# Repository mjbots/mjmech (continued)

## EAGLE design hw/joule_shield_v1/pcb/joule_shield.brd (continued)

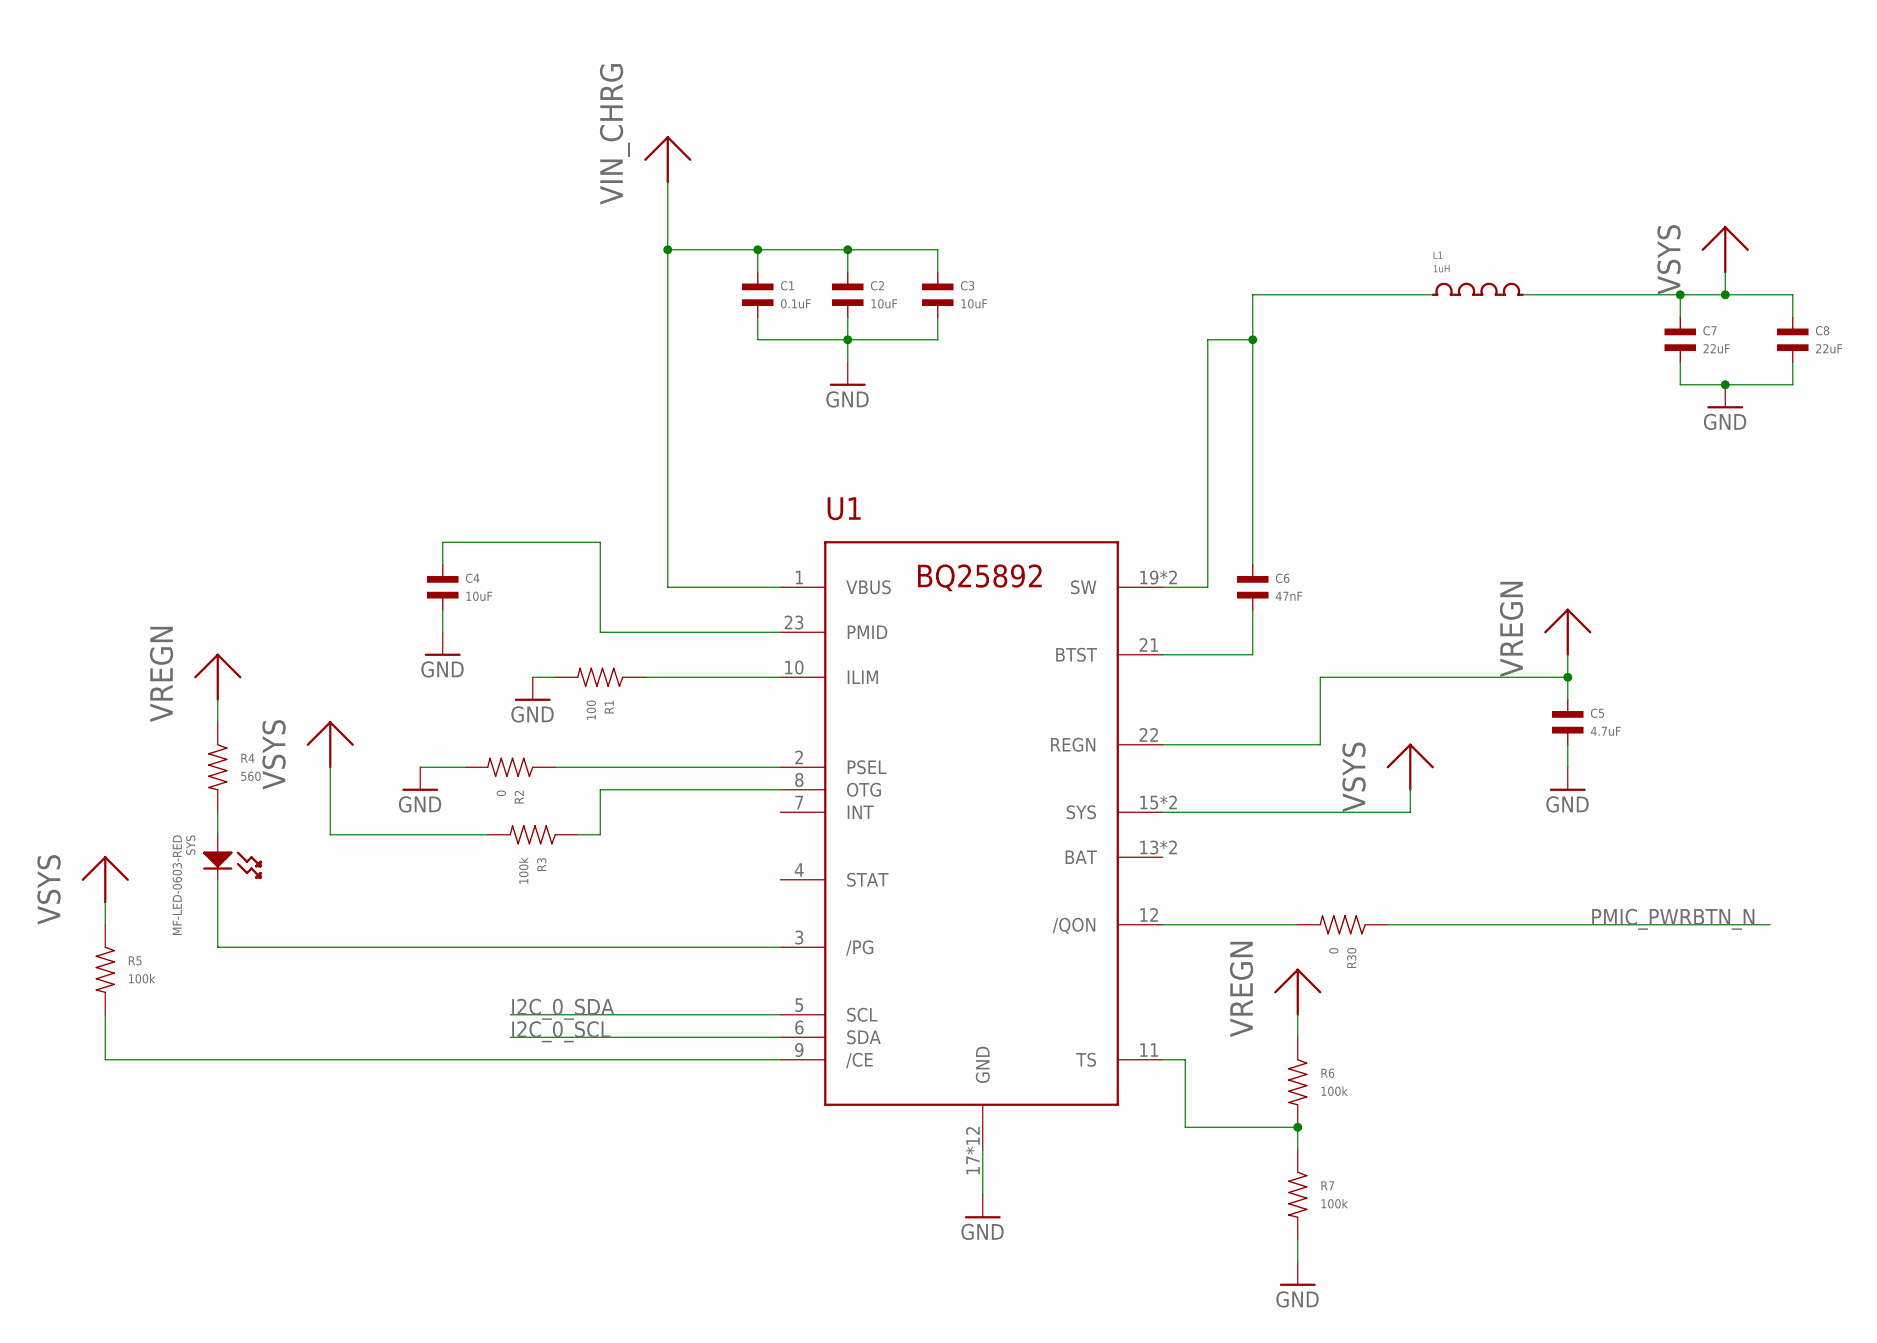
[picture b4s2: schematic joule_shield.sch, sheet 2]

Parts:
C1: 0.1uF; C0603; MPN MF-CAP-0603-0.1uF
C2, C3, C4: 10uF; C0603; MPN C1608X5R1E106M080AC
C5: 4.7uF; C0603; MPN C1608X5R1E475M080AC
C6: 47nF; C0603; MPN CGA3E2X5R1H473M080AA
C7, C8: 22uF; C0603; MPN CL10A226MP8NUNE
L1: 1uH; SPM4012; MPN SPM4012T-1R0M
R1: 100; R0603; MPN MF-RES-0603-100
R2, R30: 0; R0603; MPN MF-RES-0603-0
R3, R5, R6, R7: 100k; R0603; MPN MF-RES-0603-100K
R4: 560; R0603; MPN MF-RES-0603-560
SYS: MF-LED-0603-RED; LED0603
U1: BQ25892PWQFN-24; PWQFN-24; MPN BQ25892RTWT

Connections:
GND: C1.P$2, C2.P$2, C3.P$2, C4.P$2, C5.P$2, C7.P$2, C8.P$2, R1.P$2, R2.P$2, R7.P$2, U1.17 (GND), U1.18 (GND), U1.G0 (GND), U1.G1 (GND), U1.G2 (GND), U1.G3 (GND), U1.G4 (GND), U1.G5 (GND), U1.G6 (GND), U1.G7 (GND), U1.G8 (GND), U1.G9 (GND); also elsewhere on the board
I2C_0_SCL: U1.6 (SDA); also elsewhere on the board
I2C_0_SDA: U1.5 (SCL); also elsewhere on the board
unnamed: R4.P$2, SYS.ANODE
unnamed: C4.P$1, U1.23 (PMID)
unnamed: R1.P$1, U1.10 (ILIM)
unnamed: R2.P$1, U1.2 (PSEL)
unnamed: R3.P$1, U1.8 (OTG)
unnamed: SYS.CATHODE, U1.3 (/PG)
unnamed: R6.P$2, R7.P$1, U1.11 (TS)
unnamed: R5.P$2, U1.9 (/CE)
unnamed: C6.P$2, U1.21 (BTST)
unnamed: C6.P$1, L1.1, U1.19 (SW), U1.20 (SW)
unnamed: R30.P$2, U1.12 (/QON)
PMIC_PWRBTN_N: R30.P$1; also elsewhere on the board
VIN_CHRG: C1.P$1, C2.P$1, C3.P$1, U1.1 (VBUS); also elsewhere on the board
VREGN: C5.P$1, R4.P$1, R6.P$1, U1.22 (REGN)
VSYS: C7.P$1, C8.P$1, L1.2, R3.P$2, R5.P$1, U1.15 (SYS), U1.16 (SYS); also elsewhere on the board

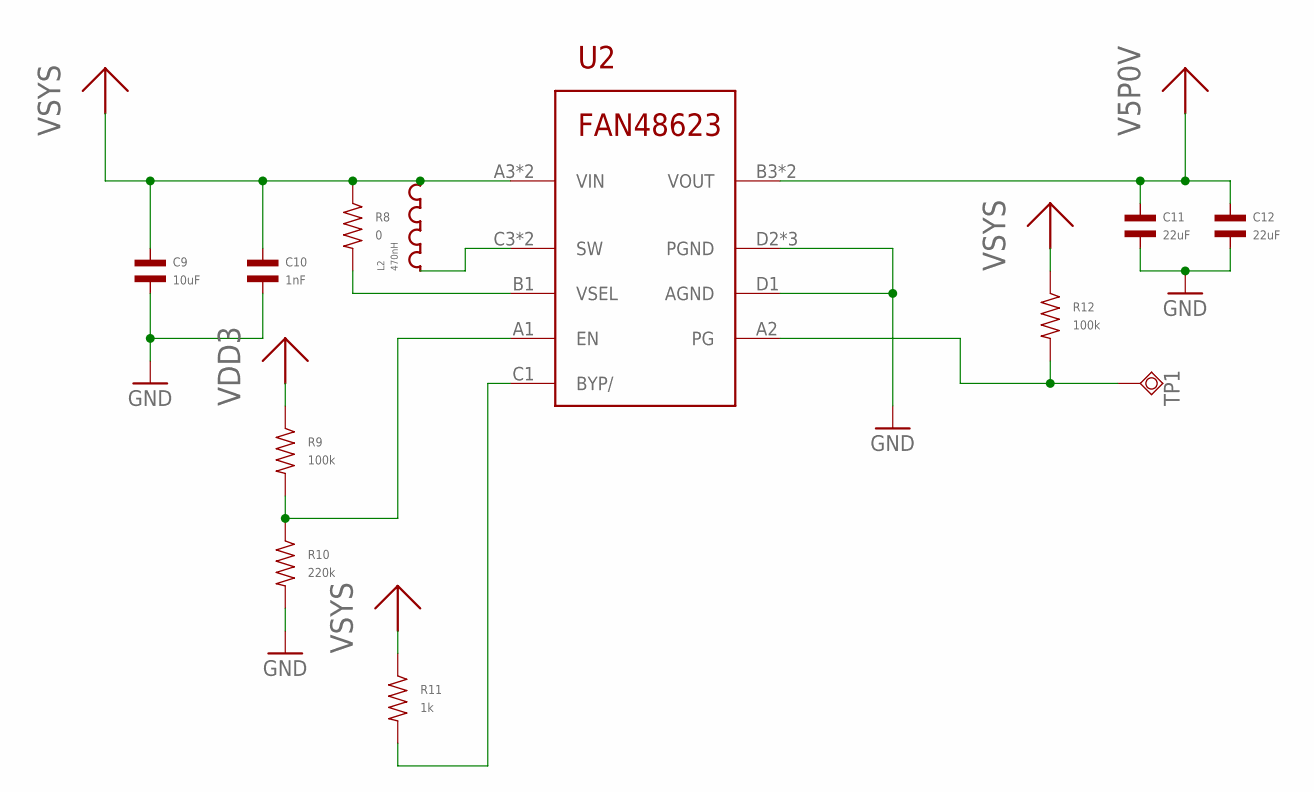
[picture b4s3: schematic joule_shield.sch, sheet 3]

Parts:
C9: 10uF; C0603; MPN C1608X5R1E106M080AC
C10: 1nF; C0603; MPN MF-CAP-0603-1nF
C11, C12: 22uF; C0603; MPN CL10A226MP8NUNE
L2: 470nH; DFE252010P; MPN DFE252010P-R47M=P2
R8: 0; R0603; MPN MF-RES-0603-0
R9, R12: 100k; R0603; MPN MF-RES-0603-100K
R10: 220k; R0603; MPN MF-RES-0603-220K
R11: 1k; R0603; MPN MF-RES-0603-1K
TP1: TPSQB1,27; B1,27
U2: FAN8623WLCSP16; WLCSP16; MPN FAN48623UC50X

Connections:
GND: C9.P$2, C10.P$2, C11.P$2, C12.P$2, R10.P$2, U2.D1 (AGND), U2.D2 (PGND), U2.D3 (PGND), U2.D4 (PGND); also elsewhere on the board
unnamed: R8.P$2, U2.B1 (VSEL)
unnamed: L2.1, U2.C3 (SW), U2.C4 (SW)
unnamed: R9.P$2, R10.P$1, U2.A1 (EN)
unnamed: R11.P$2, U2.C1 (BYP/)
unnamed: R12.P$2, TP1.TP, U2.A2 (PG)
V5P0V: C11.P$1, C12.P$1, U2.B3 (VOUT), U2.B4 (VOUT); also elsewhere on the board
VDD3: R9.P$1; also elsewhere on the board
VSYS: C9.P$1, C10.P$1, L2.2, R8.P$1, R11.P$1, R12.P$1, U2.A3 (VIN), U2.A4 (VIN); also elsewhere on the board

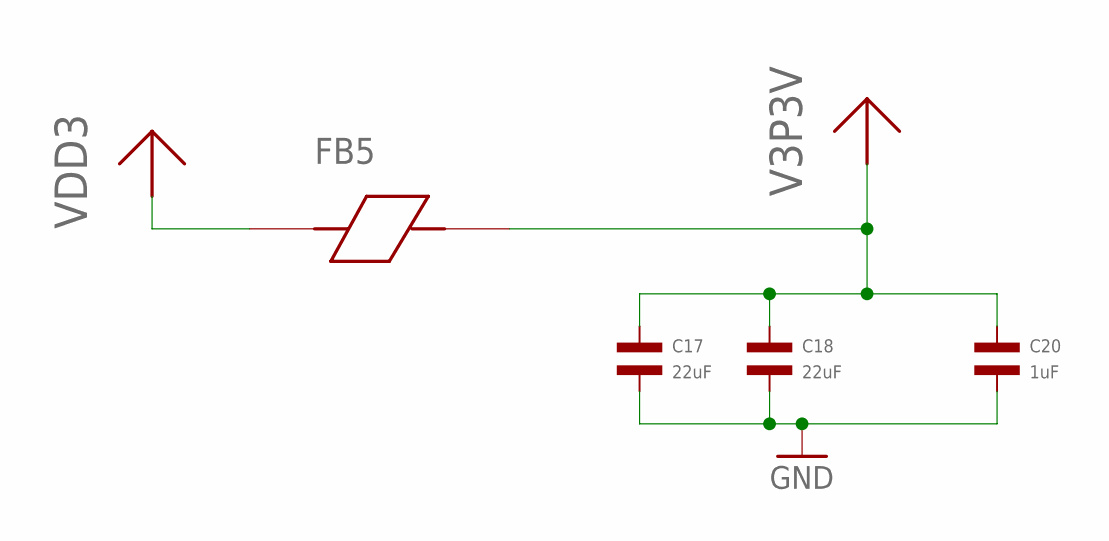
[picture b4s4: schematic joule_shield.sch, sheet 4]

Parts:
C17, C18: 22uF; C0603; MPN CL10A226MP8NUNE
C20: 1uF; C0603; MPN MF-CAP-0603-1uF
FB5: FERRITE_BEAD; R0603; MPN BLM15PD121SN1D

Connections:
GND: C17.P$2, C18.P$2, C20.P$2; also elsewhere on the board
V3P3V: C17.P$1, C18.P$1, C20.P$1, FB5.P$2; also elsewhere on the board
VDD3: FB5.P$1; also elsewhere on the board

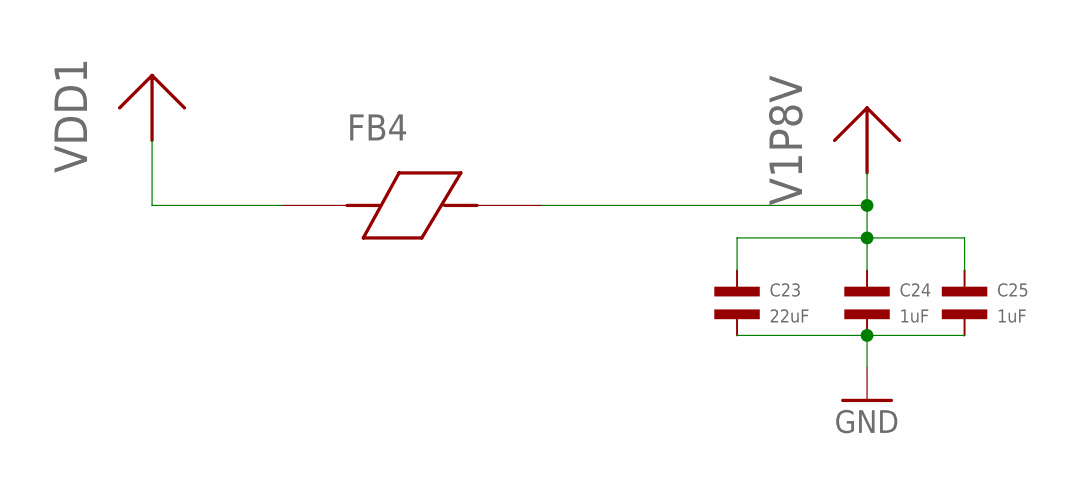
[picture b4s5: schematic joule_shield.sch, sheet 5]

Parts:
C23: 22uF; C0603; MPN CL10A226MP8NUNE
C24, C25: 1uF; C0603; MPN MF-CAP-0603-1uF
FB4: FERRITE_BEAD; R0603; MPN BLM15PD121SN1D

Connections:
GND: C23.P$2, C24.P$2, C25.P$2; also elsewhere on the board
V1P8V: C23.P$1, C24.P$1, C25.P$1, FB4.P$2; also elsewhere on the board
VDD1: FB4.P$1; also elsewhere on the board

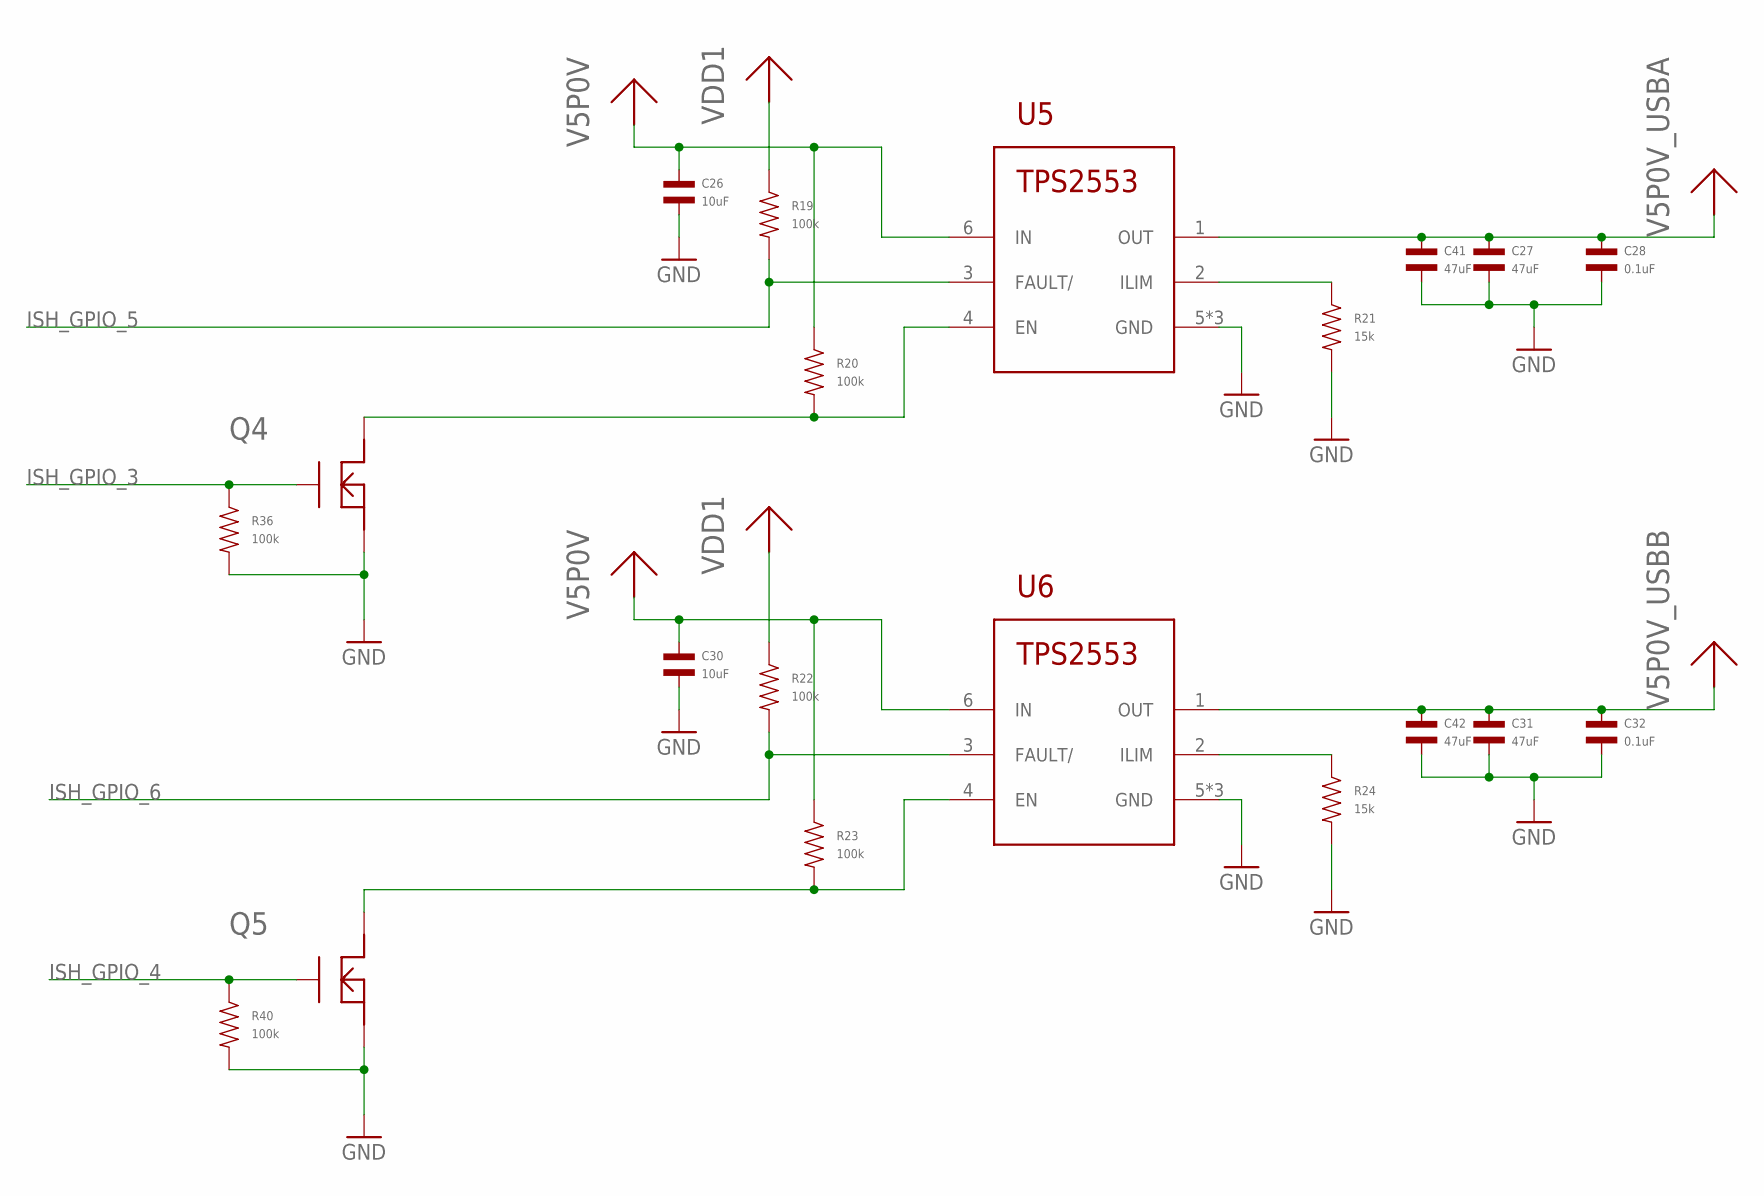
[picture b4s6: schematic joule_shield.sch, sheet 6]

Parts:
C26, C30: 10uF; C0603; MPN C1608X5R1E106M080AC
C27, C31, C41, C42: 47uF; C0805; MPN C2012X5R1A476M125AC
C28, C32: 0.1uF; C0603; MPN MF-CAP-0603-0.1uF
Q4, Q5: NFETEMT3F; EMT3F; MPN RE1C002UNTCL
R19, R20, R22, R23, R36, R40: 100k; R0603; MPN MF-RES-0603-100K
R21, R24: 15k; R0603; MPN MF-RES-0603-15K
U5, U6: TPS2553PWSON-6; PWSON-6; MPN TPS2553DRVT

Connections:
GND: C26.P$2, C27.P$2, C28.P$2, C30.P$2, C31.P$2, C32.P$2, C41.P$2, C42.P$2, Q4.2 (S), Q5.2 (S), R21.P$2, R24.P$2, R36.P$2, R40.P$2, U5.5 (GND), U5.G0 (GND), U5.G1 (GND), U6.5 (GND), U6.G0 (GND), U6.G1 (GND); also elsewhere on the board
ISH_GPIO_3: Q4.1 (G), R36.P$1; also elsewhere on the board
ISH_GPIO_4: Q5.1 (G), R40.P$1; also elsewhere on the board
ISH_GPIO_5: R19.P$2, U5.3 (FAULT/); also elsewhere on the board
ISH_GPIO_6: R22.P$2, U6.3 (FAULT/); also elsewhere on the board
unnamed: Q4.3 (D), R20.P$2, U5.4 (EN)
unnamed: R21.P$1, U5.2 (ILIM)
unnamed: Q5.3 (D), R23.P$2, U6.4 (EN)
unnamed: R24.P$1, U6.2 (ILIM)
V5P0V: C26.P$1, C30.P$1, R20.P$1, R23.P$1, U5.6 (IN), U6.6 (IN); also elsewhere on the board
V5P0V_USBA: C27.P$1, C28.P$1, C41.P$1, U5.1 (OUT); also elsewhere on the board
V5P0V_USBB: C31.P$1, C32.P$1, C42.P$1, U6.1 (OUT); also elsewhere on the board
VDD1: R19.P$1, R22.P$1; also elsewhere on the board

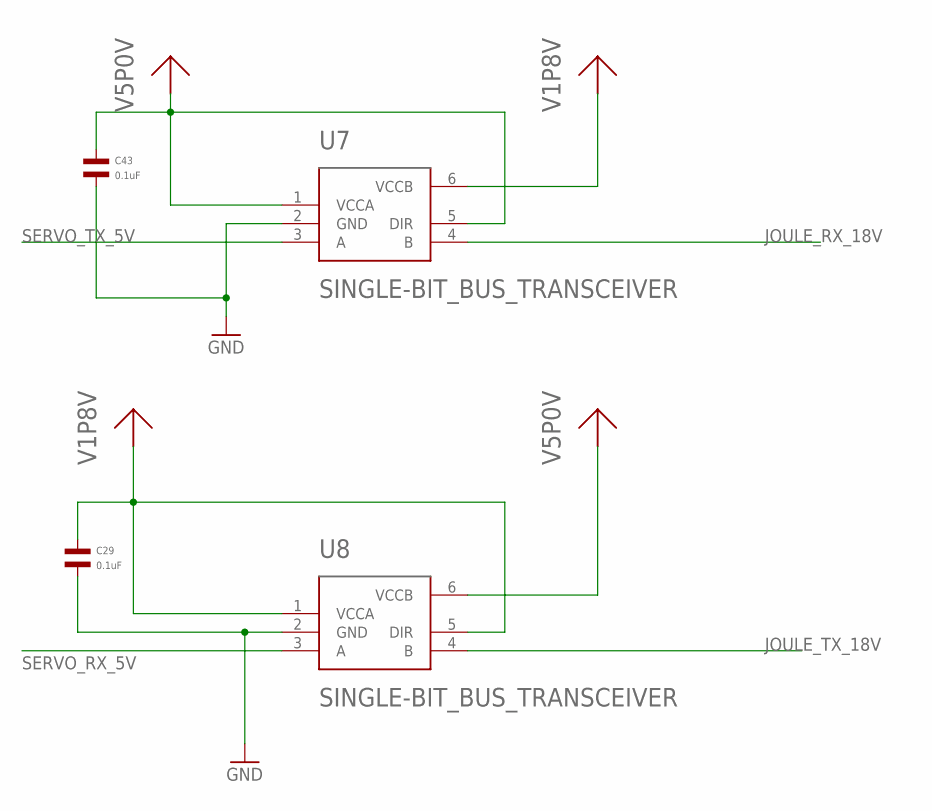
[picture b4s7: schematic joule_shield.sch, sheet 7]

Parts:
C29, C43: 0.1uF; C0603; MPN MF-CAP-0603-0.1uF
U7, U8: SINGLE-BIT_BUS_TRANSCEIVER; SOT23-6; MPN SN74LVC1T45DBVR

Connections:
GND: C29.P$2, C43.P$2, U7.2 (GND), U8.2 (GND); also elsewhere on the board
JOULE_RX_18V: U7.4 (B); also elsewhere on the board
JOULE_TX_18V: U8.4 (B); also elsewhere on the board
SERVO_RX_5V: U8.3 (A); also elsewhere on the board
SERVO_TX_5V: U7.3 (A); also elsewhere on the board
V1P8V: C29.P$1, U7.6 (VCCB), U8.1 (VCCA), U8.5 (DIR); also elsewhere on the board
V5P0V: C43.P$1, U7.1 (VCCA), U7.5 (DIR), U8.6 (VCCB); also elsewhere on the board

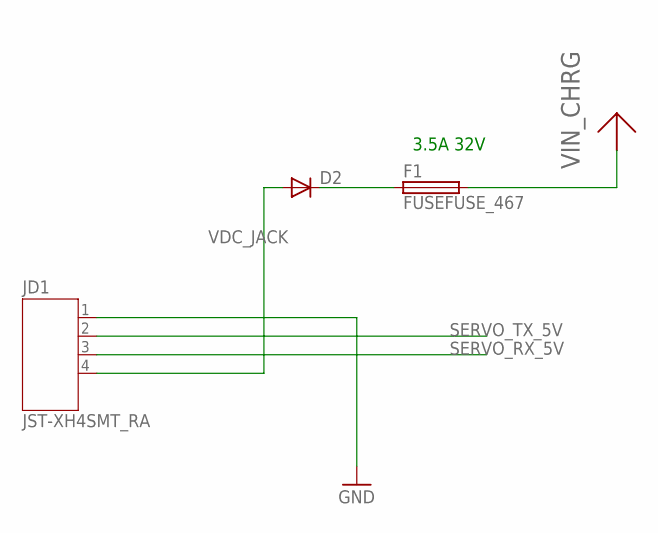
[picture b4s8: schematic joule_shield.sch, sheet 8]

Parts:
D2: DIODE-B520C; B520C; MPN B520C-13-F
F1: FUSEFUSE_467; FUSE_467; MPN 046703.5NR
JD1: JST-XH4SMT_RA; JST_XH_SMT_RA_4; MPN S4B-XH-SM4-TB(LF)(SN)

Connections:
GND: JD1.1; also elsewhere on the board
unnamed: D2.1 (C), F1.1
SERVO_RX_5V: JD1.3; also elsewhere on the board
SERVO_TX_5V: JD1.2; also elsewhere on the board
VDC_JACK: D2.2 (A), JD1.4
VIN_CHRG: F1.2; also elsewhere on the board

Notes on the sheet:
3.5A 32V

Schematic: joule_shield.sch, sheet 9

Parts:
BTN: MF-SW-TACT-4.2MM; TACT4.2MM
C37: 0.1uF; C0603; MPN MF-CAP-0603-0.1uF
D3, D5, D6, D7: ESD_DIODEM1005; M1005; MPN LXES15AAA1-133
DNX: MF-SW-TACT-4.2MM; TACT4.2MM
JFAN: AMP_MINI_FAN; AMP_MINI_292228; MPN 292228-3
JRTC: BC-2009; MPN BC-2009
PWR: MF-SW-TACT-4.2MM; TACT4.2MM
R25: 1k; R0603; MPN MF-RES-0603-1K
R27: 10k; R0603; MPN MF-RES-0603-10K
R31: 100; R0603; MPN MF-RES-0603-100
R32: 100k; R0603; MPN MF-RES-0603-100K

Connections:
BTN_N: BTN.P$2, D7.P$2; also elsewhere on the board
GND: BTN.P$3, C37.P$2, D3.P$1, D5.P$1, D6.P$1, D7.P$1, JFAN.3, JFAN.S1 (SHLD), JFAN.S2 (SHLD), JRTC.N1 (GND), PWR.P$3; also elsewhere on the board
unnamed: D3.P$2, JRTC.P1 (VBAT), JRTC.P2 (VBAT), R25.P$1
unnamed: JFAN.2, R27.P$2
unnamed: DNX.P$3, R31.P$2
unnamed: BTN.P$1, R32.P$2
PMIC_PWRBTN_N: D5.P$2, PWR.P$2; also elsewhere on the board
UART2_TX: D6.P$2, DNX.P$2; also elsewhere on the board
V3P3V: R27.P$1; also elsewhere on the board
V5P0V: C37.P$1, JFAN.1; also elsewhere on the board
VDD1: R31.P$1, R32.P$1; also elsewhere on the board
VRTC: R25.P$2; also elsewhere on the board

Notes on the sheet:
Power Button
Boot from DNX

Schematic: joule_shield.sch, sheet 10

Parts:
C33, C34, C36: 0.1uF; C0603; MPN MF-CAP-0603-0.1uF
C35: 10uF; C0603; MPN C1608X5R1E106M080AC
FB1, FB2: FERRITE_BEAD; R0603; MPN BLM15PD121SN1D
J8: DM3ATDM3AT; DM3AT; MPN DM3AT-SF-PEJM5
R26, R41, R42, R43, R44, R45: 100k; R0603; MPN MF-RES-0603-100K
U9: SN74AVCA406L; S-PBGA-N20; MPN SN74AVCA406LZXYR

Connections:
GND: C33.P$2, C34.P$2, C35.P$2, C36.P$2, J8.6 (VSS), J8.9 (CDB), J8.G0 (GND), J8.G1 (GND), J8.G2 (GND), J8.G3 (GND), U9.B3 (GND), U9.C3 (GND); also elsewhere on the board
unnamed: J8.8 (DAT1), R44.P$2, U9.D1 (DAT1B)
unnamed: J8.1 (DAT2), R43.P$2, U9.C4 (DAT2B)
unnamed: J8.2 (CD/DAT3), R42.P$2, U9.D4 (DAT3B)
unnamed: J8.3 (CMD), R41.P$2, U9.C2 (CMDB)
unnamed: J8.5 (CLK), U9.D3 (CLKB)
unnamed: J8.7 (DAT0), R45.P$2, U9.D2 (DAT0B)
SDCARD_CD: J8.11 (CDA), R26.P$2; also elsewhere on the board
SDCARD_CLK: U9.A3 (CLKA); also elsewhere on the board
SDCARD_CLK_FB: U9.A1 (CLKF); also elsewhere on the board
SDCARD_CMD: U9.B1 (CMDA); also elsewhere on the board
SDCARD_D0: U9.B2 (DAT0A); also elsewhere on the board
SDCARD_D1: U9.A2 (DAT1A); also elsewhere on the board
SDCARD_D2: U9.B4 (DAT2A); also elsewhere on the board
SDCARD_D3: U9.A4 (DAT3A); also elsewhere on the board
SDCARD_LVL_CMD_DIR: U9.B5 (CMD_DIR); also elsewhere on the board
SDCARD_LVL_DAT_DIR: U9.C1 (DAT123_DIR), U9.C5 (DAT0_DIR); also elsewhere on the board
SDCARD_VCCA: C33.P$1, FB1.P$2, R26.P$1, U9.A5 (VCCA)
SDCARD_VCCB: C34.P$1, C35.P$1, C36.P$1, FB2.P$1, J8.4 (VDD), R41.P$1, R42.P$1, R43.P$1, R44.P$1, R45.P$1, U9.D5 (VCCB)
V1P8V: FB1.P$1; also elsewhere on the board
V3P3V: FB2.P$2; also elsewhere on the board

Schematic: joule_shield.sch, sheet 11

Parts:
C38, C39, C40: 0.1uF; C0603; MPN MF-CAP-0603-0.1uF
D1, D8: MF-DIO-SOD123-BAT42; SOD-123
D4: ESD_DIODEM1005; M1005; MPN LXES15AAA1-133
FB3: FERRITE_BEAD; R0603; MPN BLM15PD121SN1D
J1: MF-CON-MICROUSB-RIGHT; MICROUSB-RIGHT
R28, R29: 27; R0603; MPN MF-RES-0603-27
U10: FT231XQFN-20; QFN-20; MPN FT231XQ-R

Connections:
GND: C38.P$2, C39.P$2, C40.P$2, D4.P$1, J1.5 (GND), J1.S1 (SLD), J1.S2 (SLD), J1.S3 (SLD), J1.S4 (SLD), J1.S5 (SLD), J1.S6 (SLD), U10.3 (AGND), U10.13 (GND), U10.G0 (GND); also elsewhere on the board
unnamed: D1.ANODE, FB3.P$2
unnamed: R28.P$2, U10.9 (USBDM)
unnamed: D4.P$2, FB3.P$1, J1.1 (5V)
unnamed: R29.P$2, U10.8 (USBDP)
unnamed: J1.3 (D+), R29.P$1
unnamed: C38.P$1, D1.CATHODE, D8.CATHODE, U10.12 (VCC)
unnamed: J1.2 (D-), R28.P$1
unnamed: C40.P$1, U10.10 (3V3OUT)
UART2_CTS: U10.19 (RTS/); also elsewhere on the board
UART2_RTS: U10.6 (CTS/); also elsewhere on the board
UART2_RX: U10.17 (TXD); also elsewhere on the board
UART2_TX: U10.1 (RXD); also elsewhere on the board
V1P8V: C39.P$1, U10.20 (VCCIO); also elsewhere on the board
V5P0V: D8.ANODE; also elsewhere on the board

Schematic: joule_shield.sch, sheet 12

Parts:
LED1, LED2: MF-LED-0603-RED; LED0603
LED3: MF-LED-0603-GREEN; LED0603
Q1, Q2, Q3: NFETEMT3F; EMT3F; MPN RE1C002UNTCL
R33, R34, R35: 1k; R0603; MPN MF-RES-0603-1K
R37, R38, R39: 470; R0603; MPN MF-RES-0603-470

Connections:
GND: Q1.2 (S), Q2.2 (S), Q3.2 (S), R33.P$1, R34.P$1, R35.P$1; also elsewhere on the board
ISH_GPIO_0: Q1.1 (G), R33.P$2; also elsewhere on the board
ISH_GPIO_1: Q2.1 (G), R34.P$2; also elsewhere on the board
ISH_GPIO_2: Q3.1 (G), R35.P$2; also elsewhere on the board
unnamed: LED3.ANODE, R39.P$2
unnamed: LED2.ANODE, R38.P$2
unnamed: LED1.ANODE, R37.P$2
unnamed: LED1.CATHODE, Q1.3 (D)
unnamed: LED2.CATHODE, Q2.3 (D)
unnamed: LED3.CATHODE, Q3.3 (D)
VSYS: R37.P$1, R38.P$1, R39.P$1; also elsewhere on the board

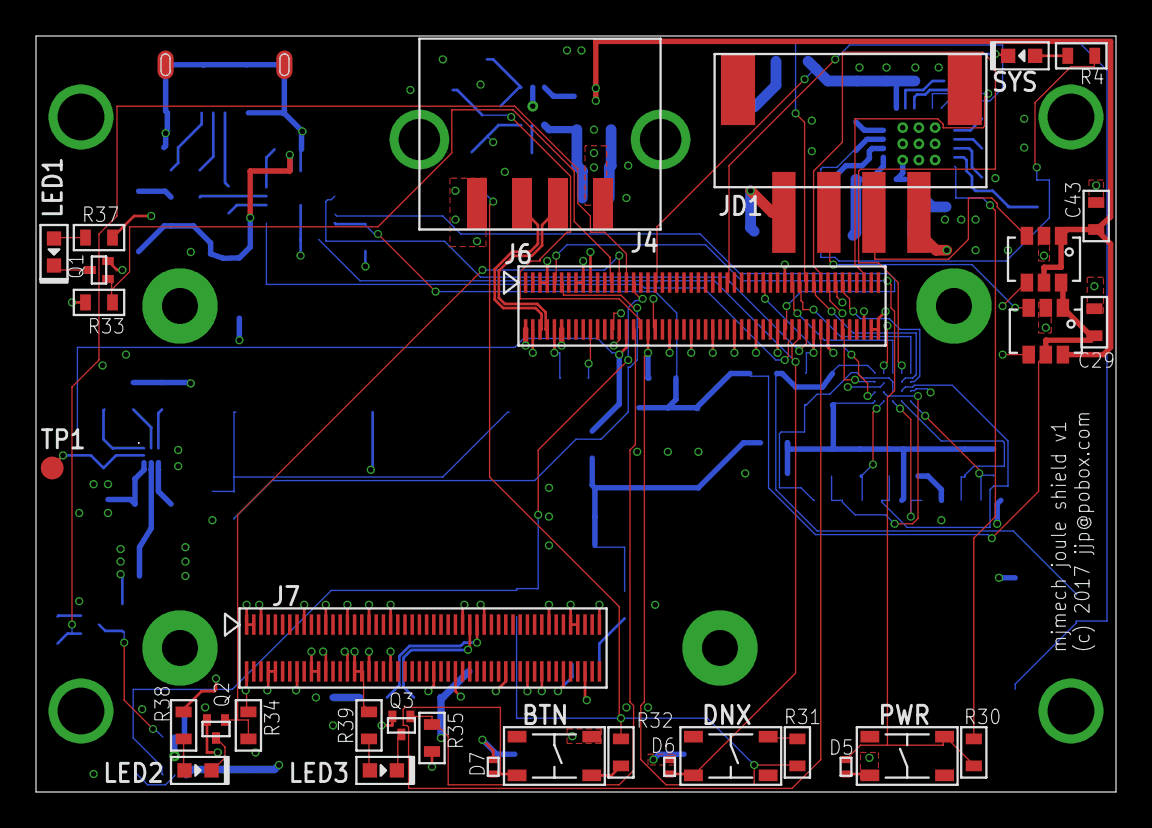
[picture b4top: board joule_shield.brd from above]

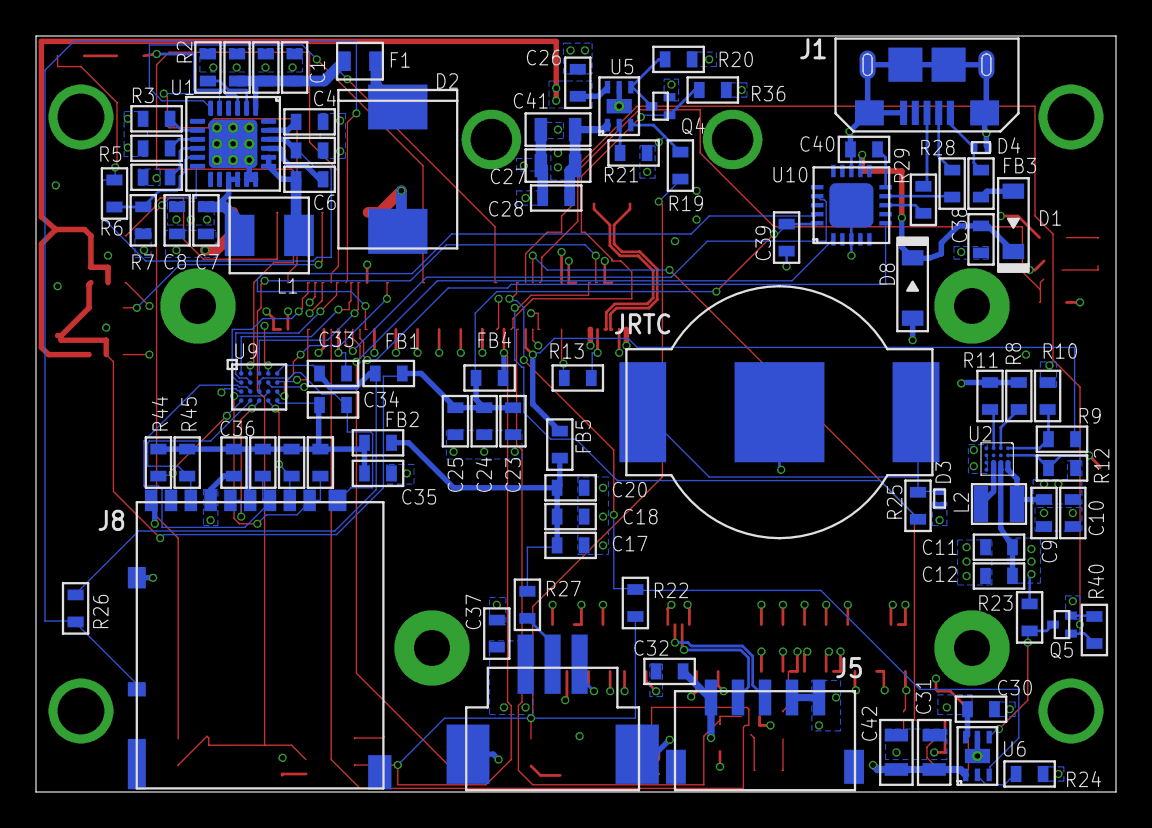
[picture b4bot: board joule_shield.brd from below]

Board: 4 copper layers, 60.0 x 42.0 mm, 130 parts (90 on the bottom side), 94 nets.

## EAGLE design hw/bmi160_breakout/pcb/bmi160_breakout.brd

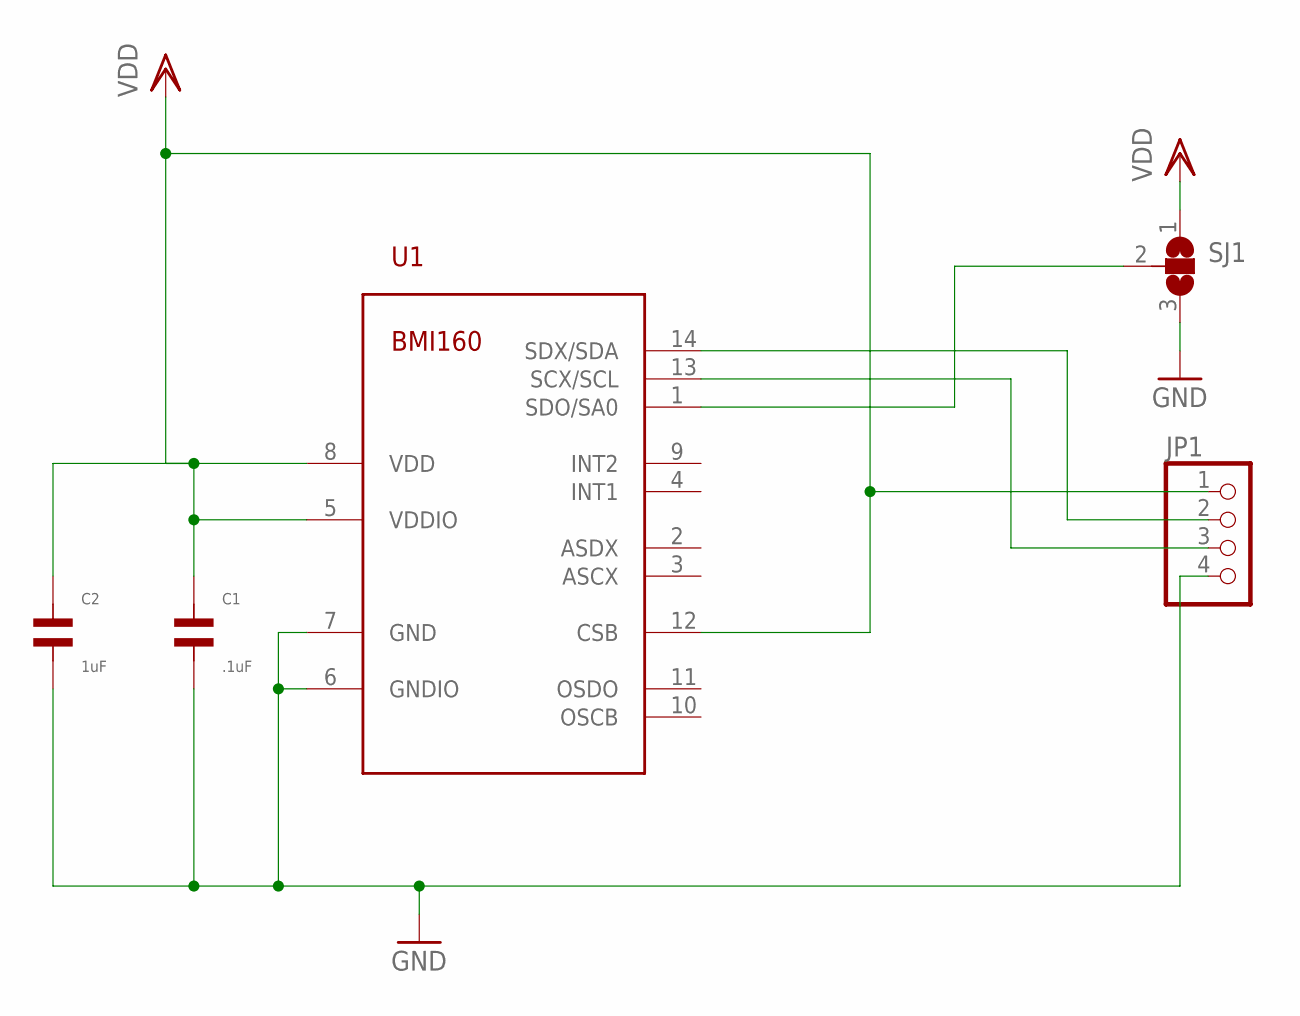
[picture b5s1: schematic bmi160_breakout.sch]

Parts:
C1: .1uF; C0603
C2: 1uF; C0805
JP1: PINHD-1X4; 1X04
SJ1: SJ2W; SJ_2
U1: BMI160LGA14; LGA14; MOUSER_PN 262-BMI160

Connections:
GND: C1.P$2, C2.P$2, JP1.4, SJ1.3, U1.6 (GNDIO), U1.7 (GND)
unnamed: SJ1.2, U1.1 (SDO/SA0)
SCL: JP1.3, U1.13 (SCX/SCL)
SDA: JP1.2, U1.14 (SDX/SDA)
VDD: C1.P$1, C2.P$1, JP1.1, SJ1.1, U1.5 (VDDIO), U1.8 (VDD), U1.12 (CSB)

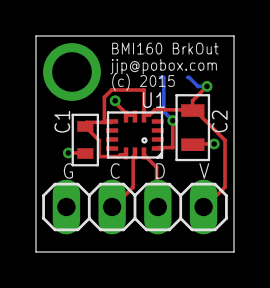
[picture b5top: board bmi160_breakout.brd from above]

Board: 2 copper layers, 11.0 x 12.0 mm, 5 parts (1 on the bottom side), 5 nets.

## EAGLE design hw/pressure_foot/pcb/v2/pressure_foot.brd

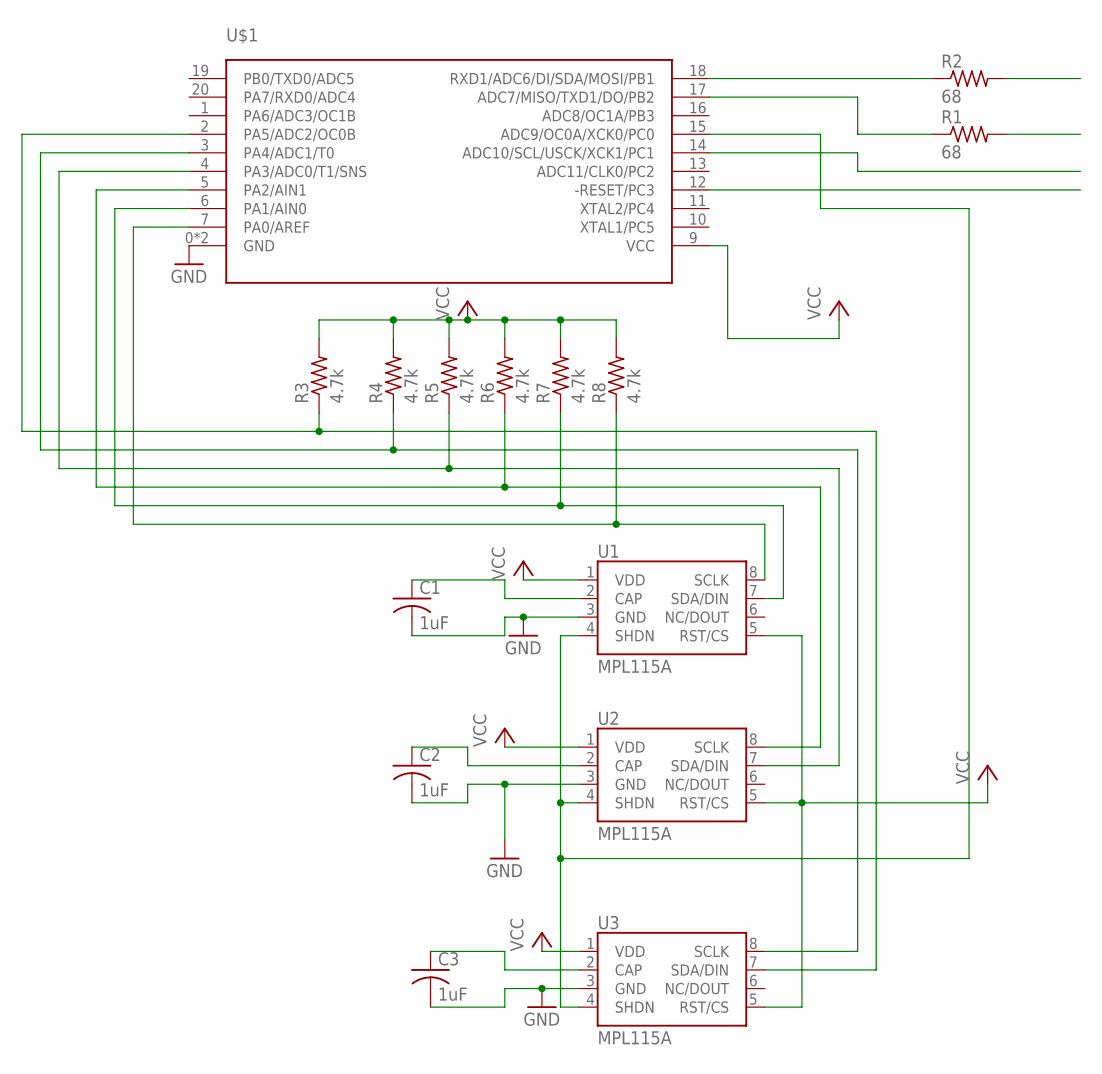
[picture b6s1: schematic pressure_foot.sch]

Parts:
C1, C2, C3: 1uF; C0603
R1, R2: 68; R0603
R3, R4, R5, R6, R7, R8: 4.7k; R0603
U1, U2, U3: MPL115A; LGA8
U$1: ATTINY1634QFN20; QFN20

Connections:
GND: C1.2, C2.2, C3.2, U1.3 (GND), U2.3 (GND), U3.3 (GND), U$1.0 (GND), U$1.8 (GND)
unnamed: R8.1, U1.8 (SCLK), U$1.7 (PA0/AREF)
unnamed: R2.1, U$1.18 (RXD1/ADC6/DI/SDA/MOSI/PB1)
unnamed: R1.1, U$1.17 (ADC7/MISO/TXD1/DO/PB2)
unnamed: C1.1, U1.2 (CAP)
unnamed: C3.1, U3.2 (CAP)
unnamed: R6.1, U2.8 (SCLK), U$1.5 (PA2/AIN1)
unnamed: R5.1, U2.7 (SDA/DIN), U$1.4 (PA3/ADC0/T1/SNS)
unnamed: U1.4 (SHDN), U2.4 (SHDN), U3.4 (SHDN), U$1.15 (ADC9/OC0A/XCK0/PC0)
unnamed: C2.1, U2.2 (CAP)
unnamed: R7.1, U1.7 (SDA/DIN), U$1.6 (PA1/AIN0)
unnamed: R4.1, U3.8 (SCLK), U$1.3 (PA4/ADC1/T0)
unnamed: R3.1, U3.7 (SDA/DIN), U$1.2 (PA5/ADC2/OC0B)
VCC: R3.2, R4.2, R5.2, R6.2, R7.2, R8.2, U1.1 (VDD), U1.5 (RST/CS), U2.1 (VDD), U2.5 (RST/CS), U3.1 (VDD), U3.5 (RST/CS), U$1.9 (VCC)

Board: 2 copper layers, 15 parts (3 on the bottom side), 14 nets, no tracks yet.
